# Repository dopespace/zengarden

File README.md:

# zengarden
dope space zen garden is a set of star lanterns that move up and down in the the  Georgia Tech Architecture West building atrium

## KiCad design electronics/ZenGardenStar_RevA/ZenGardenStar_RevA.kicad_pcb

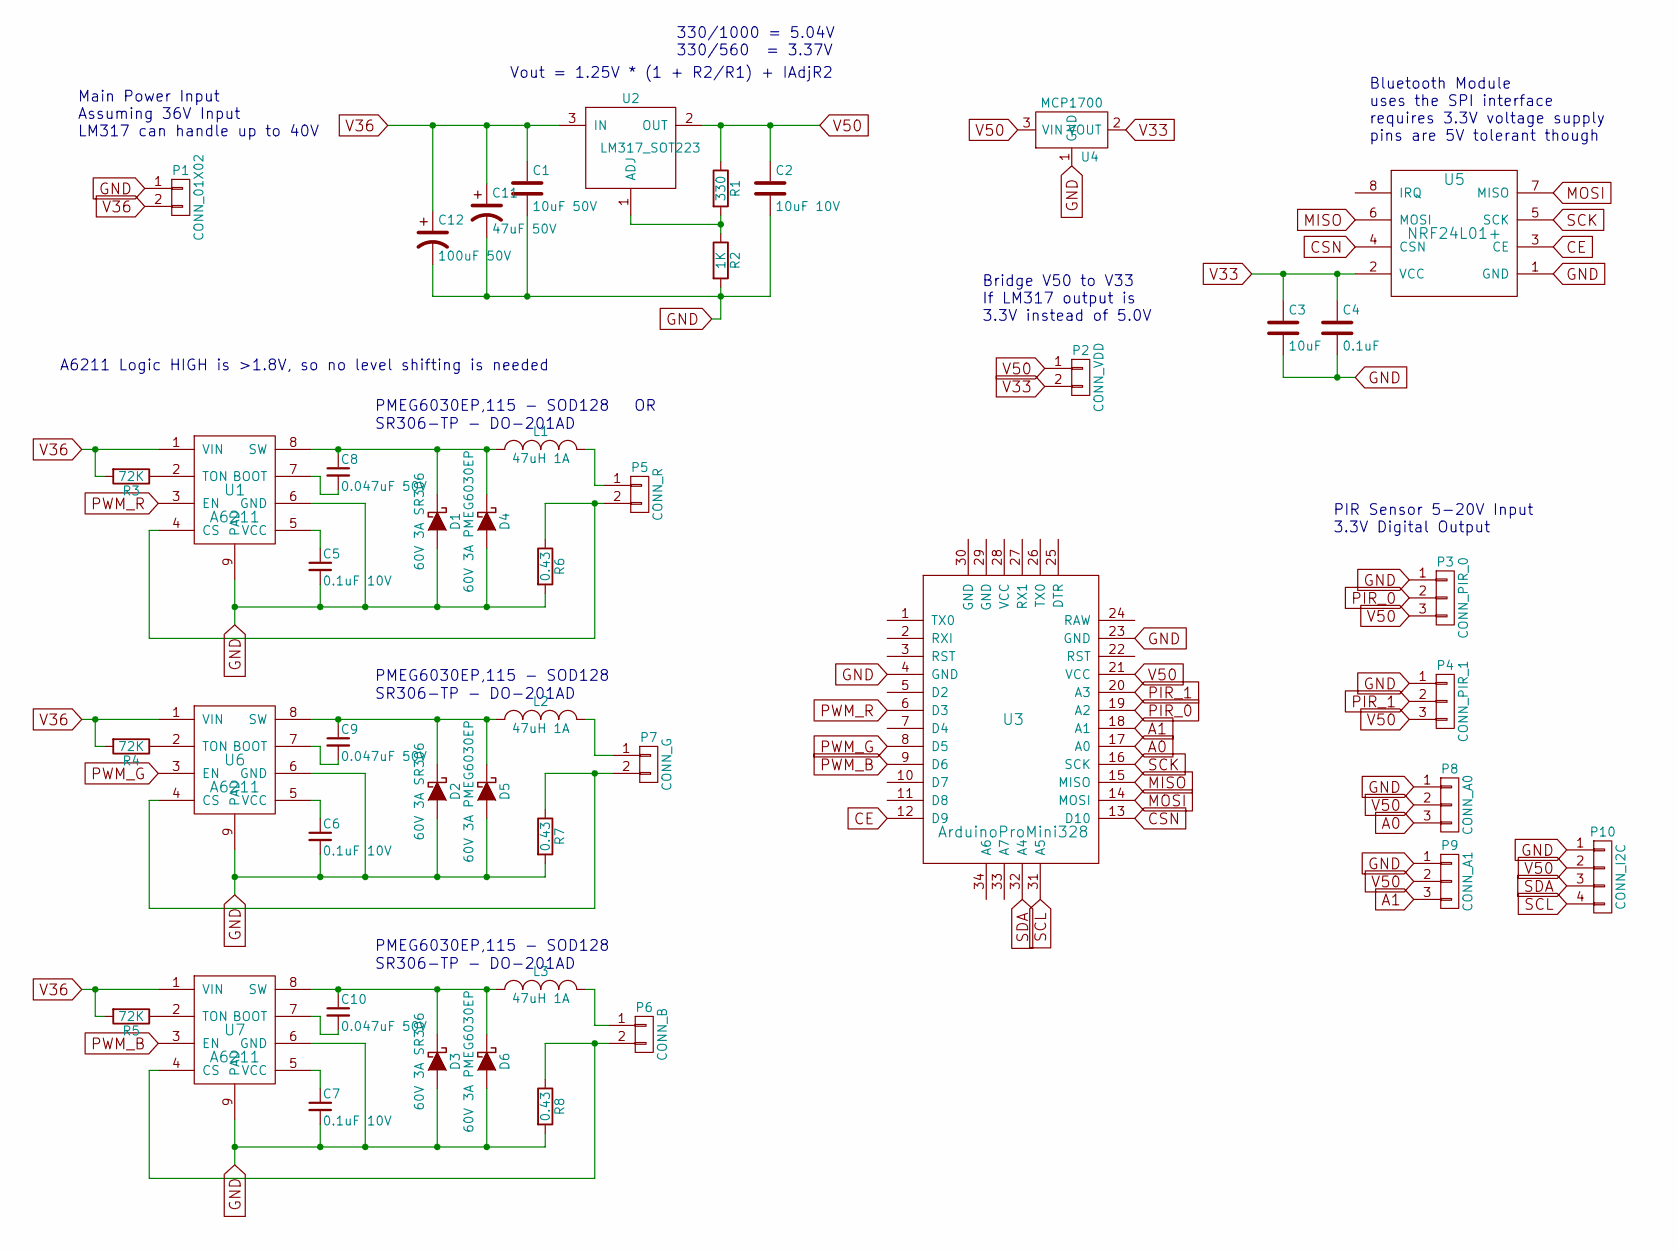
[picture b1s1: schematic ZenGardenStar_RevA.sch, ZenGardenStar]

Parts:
C1: 10uF 50V; C_1206
C2: 10uF 10V; C_1206
C3: 10uF; C_1206
C4: 0.1uF; C_0805
C5, C6, C7: 0.1uF 10V; C_0805
C8, C9, C10: 0.047uF 50V; C_0805
C11: 47uF 50V; C_Radial_D7.5_L11.2_P2.5
C12: 100uF 50V; C_Radial_D8_L13_P3.8
D1, D2, D3: 60V 3A SR306; Diode_DO-201AD_Horizontal_RM15
D4, D5, D6: 60V 3A PMEG6030EP; SOD-123
L1, L2, L3: 47uH 1A; TAIYO_YUDEN_IND_6045
P1: CONN_01X02; AK300-2
P2: CONN_VDD; Pin_Header_Straight_1x02
P3: CONN_PIR_0; Pin_Header_Straight_1x03
P4: CONN_PIR_1; Pin_Header_Straight_1x03
P5: CONN_R; AK300-2
P6: CONN_B; AK300-2
P7: CONN_G; AK300-2
P8: CONN_A0; Pin_Header_Straight_1x03
P9: CONN_A1; Pin_Header_Straight_1x03
P10: CONN_I2C; Pin_Header_Straight_1x04
R1: 330; R_1206
R2: 1K; R_1206
R3, R4, R5: 72K; R_1206
R6, R7, R8: 0.43; R_1206
U1, U6, U7: A6211; SOIC-8-1EP_3.9x4.9mm_Pitch1.27mm
U2: LM317_SOT223; SOT-223
U3: ArduinoProMini328
U4: MCP1700; SOT-23
U5: NRF24L01+

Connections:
A0: P8.3, U3.17 (A0)
A1: P9.3, U3.18 (A1)
CE: U3.12 (D9), U5.3 (CE)
CSN: U3.13 (D10), U5.4 (CSN)
GND: C1.2, C2.2, C3.2, C4.2, C5.2, C6.2, C7.2, C11.2, C12.2, D1.2 (A), D2.2 (A), D3.2 (A), D4.2 (A), D5.2 (A), D6.2 (A), P1.1, P3.1, P4.1, P8.1, P9.1, P10.1, R2.2, R6.2, R7.2, R8.2, U1.6 (GND), U1.9 (PAD), U3.4 (GND), U3.23 (GND), U4.1 (GND), U5.1 (GND), U6.6 (GND), U6.9 (PAD), U7.6 (GND), U7.9 (PAD)
MISO: U3.15 (MISO), U5.6 (MOSI)
MOSI: U3.14 (MOSI), U5.7 (MISO)
unnamed: C5.1, U1.5 (VCC)
unnamed: C6.1, U6.5 (VCC)
unnamed: C7.1, U7.5 (VCC)
unnamed: C8.1, D1.1 (K), D4.1 (K), L1.1, U1.8 (SW)
unnamed: C8.2, U1.7 (BOOT)
unnamed: C9.1, D2.1 (K), D5.1 (K), L2.1, U6.8 (SW)
unnamed: C9.2, U6.7 (BOOT)
unnamed: C10.1, D3.1 (K), D6.1 (K), L3.1, U7.8 (SW)
unnamed: C10.2, U7.7 (BOOT)
unnamed: L1.2, P5.1
unnamed: L2.2, P7.1
unnamed: L3.2, P6.1
unnamed: P5.2, R6.1, U1.4 (CS)
unnamed: P6.2, R8.1, U7.4 (CS)
unnamed: P7.2, R7.1, U6.4 (CS)
unnamed: R1.2, R2.1, U2.1 (ADJ)
unnamed: R3.1, U1.2 (TON)
unnamed: R4.1, U6.2 (TON)
unnamed: R5.1, U7.2 (TON)
PIR_0: P3.2, U3.19 (A2)
PIR_1: P4.2, U3.20 (A3)
PWM_B: U3.9 (D6), U7.3 (EN)
PWM_G: U3.8 (D5), U6.3 (EN)
PWM_R: U1.3 (EN), U3.6 (D3)
SCK: U3.16 (SCK), U5.5 (SCK)
SCL: P10.4, U3.31 (A5)
SDA: P10.3, U3.32 (A4)
V33: C3.1, C4.1, P2.2, U4.2 (VOUT), U5.2 (VCC)
V36: C1.1, C11.1, C12.1, P1.2, R3.2, R4.2, R5.2, U1.1 (VIN), U2.3 (IN), U6.1 (VIN), U7.1 (VIN)
V50: C2.1, P2.1, P3.3, P4.3, P8.2, P9.2, P10.2, R1.1, U2.2 (OUT), U3.21 (VCC), U4.3 (VIN)

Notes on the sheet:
Bluetooth Module uses the SPI interface requires 3.3V voltage supply pins are 5V tolerant though
Vout = 1.25V * (1 + R2/R1) + IAdjR2
330/1000 = 5.04V 330/560 = 3.37V
Bridge V50 to V33 If LM317 output is 3.3V instead of 5.0V
Main Power Input Assuming 36V Input LM317 can handle up to 40V
A6211 Logic HIGH is >1.8V, so no level shifting is needed
PMEG6030EP,115 - SOD128 OR
SR306-TP - DO-201AD
PMEG6030EP,115 - SOD128
PIR Sensor 5-20V Input 3.3V Digital Output

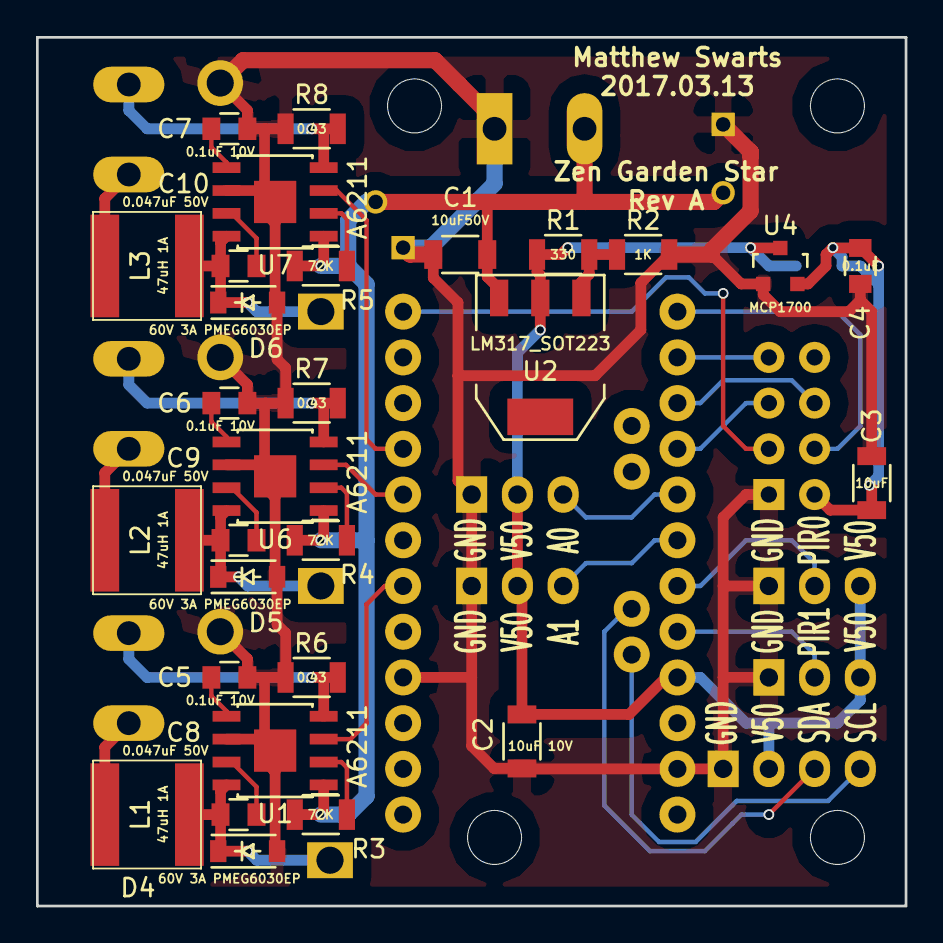
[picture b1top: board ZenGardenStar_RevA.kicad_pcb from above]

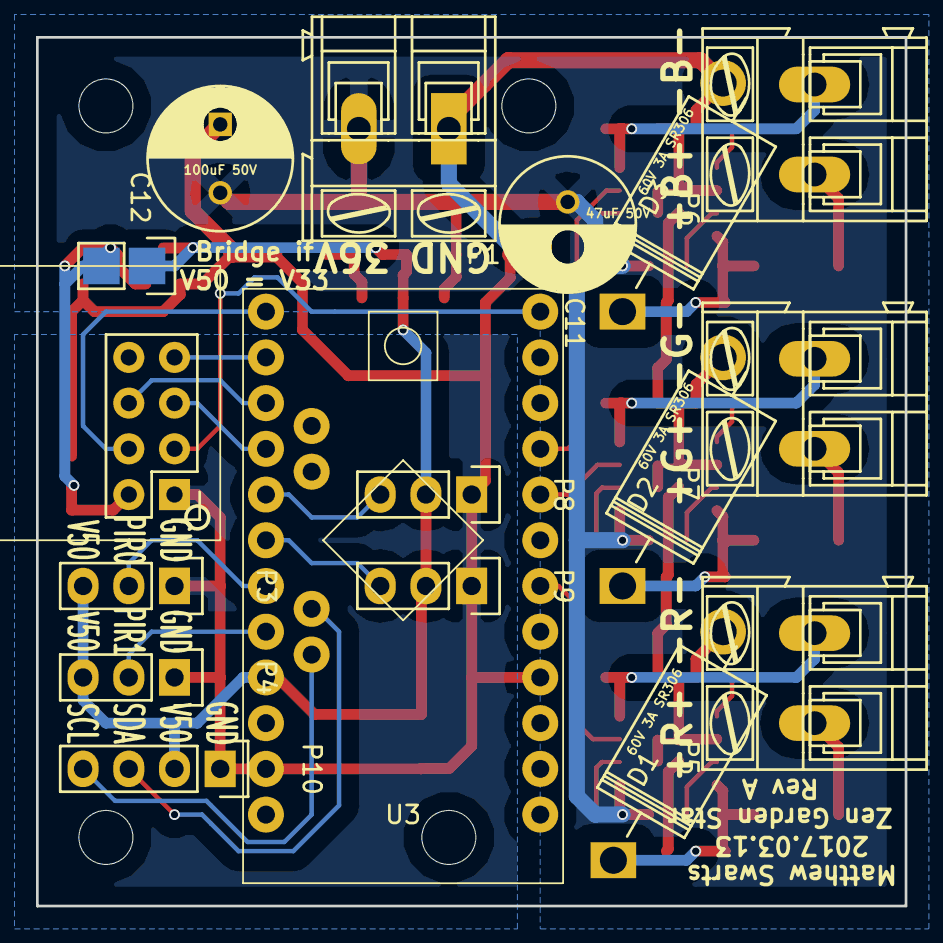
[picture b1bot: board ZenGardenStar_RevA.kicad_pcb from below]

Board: 2 copper layers, 48.3 x 48.3 mm, 46 parts (17 on the bottom side), 37 nets.

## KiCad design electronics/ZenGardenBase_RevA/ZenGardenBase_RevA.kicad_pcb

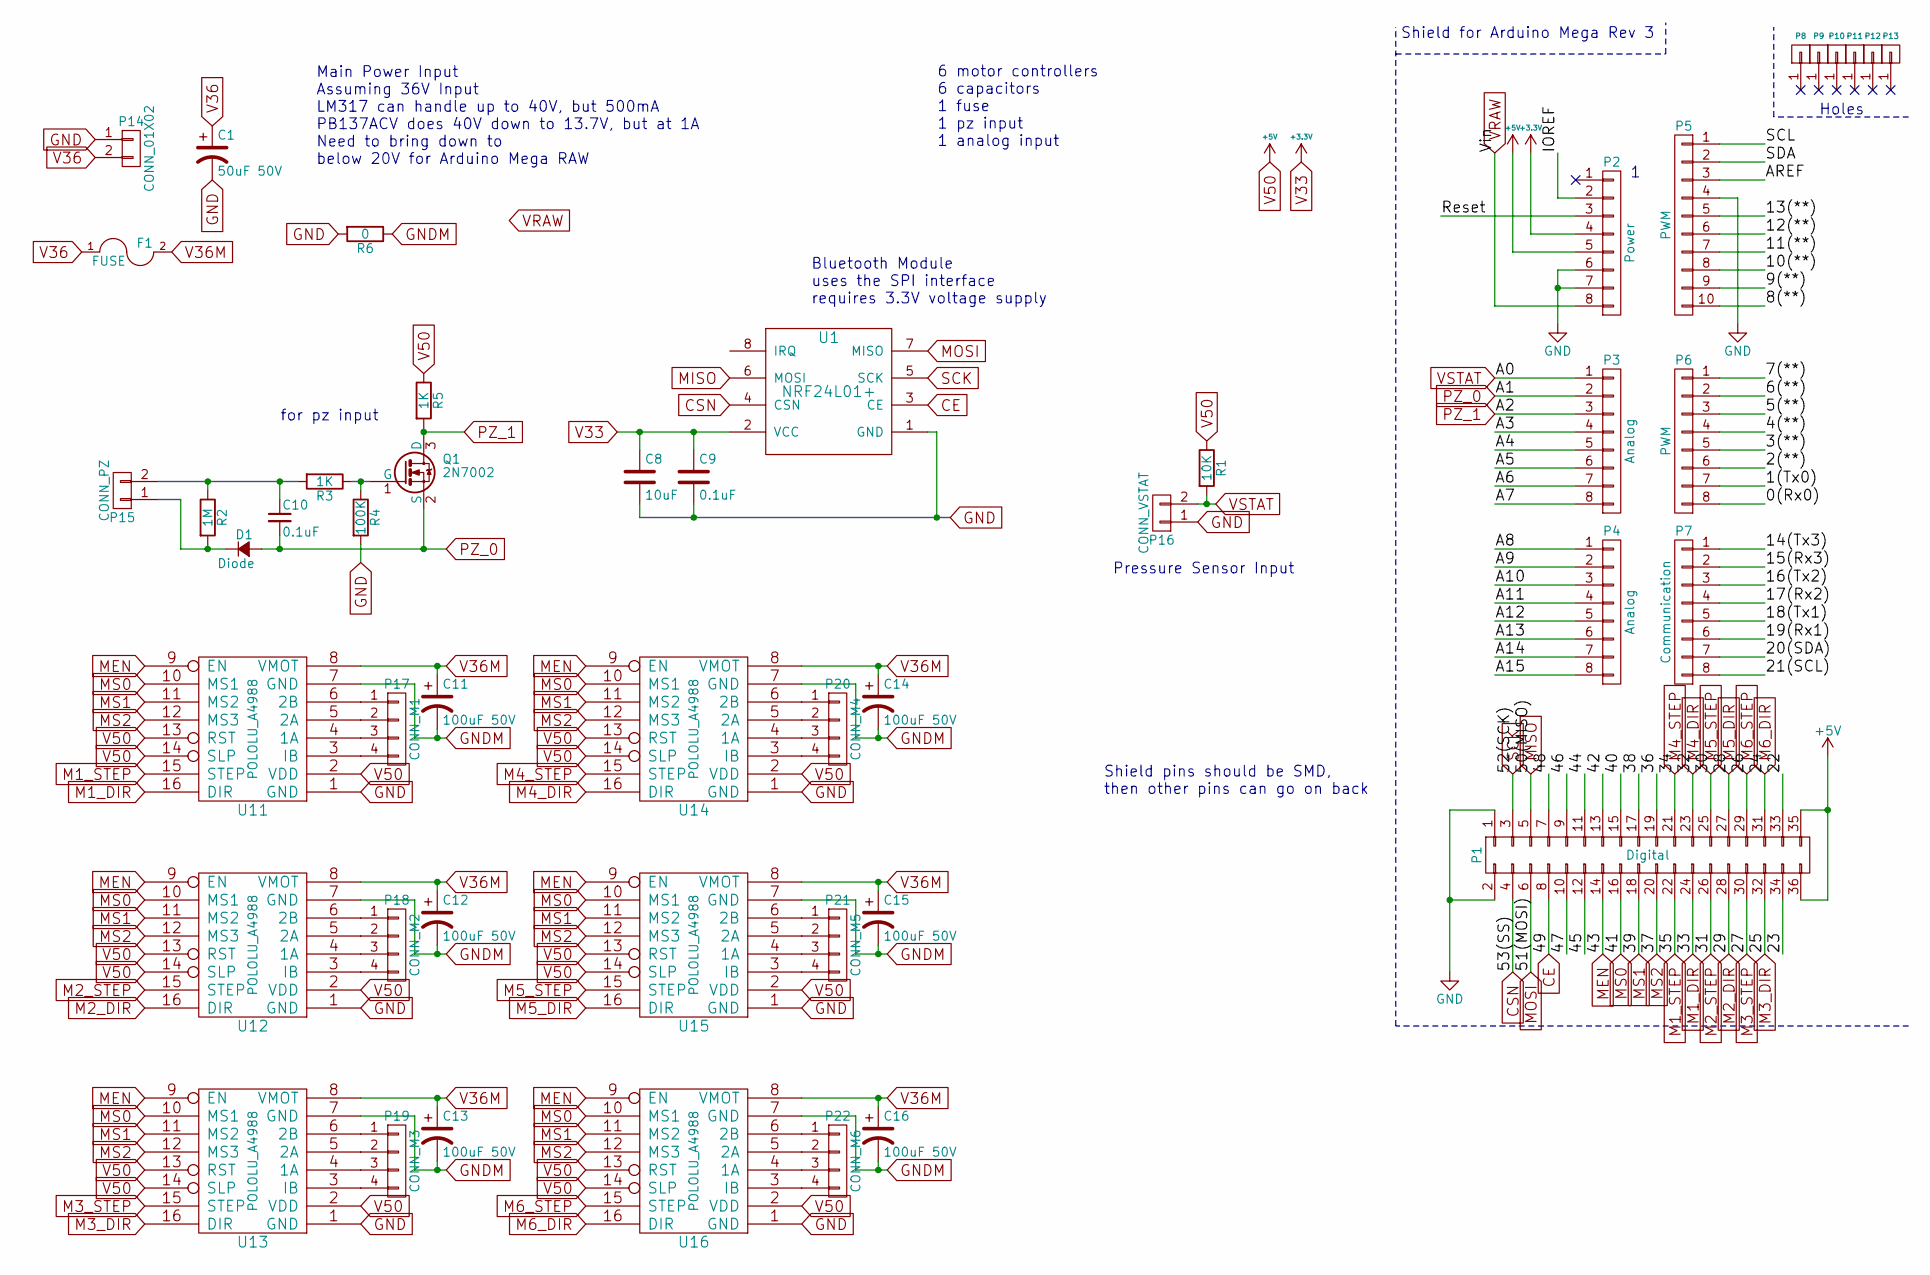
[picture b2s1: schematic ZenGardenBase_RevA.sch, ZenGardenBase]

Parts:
C1: 50uF 50V; C_Radial_D6.3_L11.2_P2.5
C8: 10uF; C_1206
C9, C10: 0.1uF; C_0805
C11, C12, C13, C14, C15, C16: 100uF 50V; C_Radial_D8_L13_P3.8
D1: Diode; SOD-123
F1: FUSE; Fuse_TE5_Littlefuse-395Series
P1: Digital; Socket_Strip_Arduino_2x18
P2: Power; Socket_Strip_Arduino_1x08
P3, P4: Analog; Socket_Strip_Arduino_1x08
P5: PWM; Socket_Strip_Arduino_1x10
P6: PWM; Socket_Strip_Arduino_1x08
P7: Communication; Socket_Strip_Arduino_1x08
P8, P9, P10, P11, P12, P13: CONN_01X01; Arduino_1pin
P14: CONN_01X02; AK300-2
P15: CONN_PZ; Pin_Header_Straight_1x02
P16: CONN_VSTAT; Pin_Header_Straight_1x02
P17: CONN_M1; AK300-4
P18: CONN_M2; AK300-4
P19: CONN_M3; AK300-4
P20: CONN_M4; AK300-4
P21: CONN_M5; AK300-4
P22: CONN_M6; AK300-4
Q1: 2N7002; SOT-23
R1: 10K; R_1206
R2: 1M; R_1206
R3, R5: 1K; R_1206
R4: 100K; R_1206
R6: 0; R_1206
U1: NRF24L01+
U11, U12, U13, U14, U15, U16: POLOLU_A4988; SWDIP8_.6W

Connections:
/0(Rx0): P6.8
/1(Tx0): P6.7
/2(**): P6.6
/3(**): P6.5
/4(**): P6.4
/5(**): P6.3
/6(**): P6.2
/7(**): P6.1
/8(**): P5.10
/9(**): P5.9
/10(**): P5.8
/11(**): P5.7
/12(**): P5.6
/13(**): P5.5
/14(Tx3): P7.1
/15(Rx3): P7.2
/16(Tx2): P7.3
/17(Rx2): P7.4
/18(Tx1): P7.5
/19(Rx1): P7.6
/20(SDA): P7.7
/21(SCL): P7.8
/22: P1.33
/23: P1.34
/36: P1.19
/38: P1.17
/40: P1.15
/42: P1.13
/44: P1.11
/45: P1.12
/46: P1.9
/47: P1.10
/48: P1.7
/A3: P3.4
/A4: P3.5
/A5: P3.6
/A6: P3.7
/A7: P3.8
/A8: P4.1
/A9: P4.2
/A10: P4.3
/A11: P4.4
/A12: P4.5
/A13: P4.6
/A14: P4.7
/A15: P4.8
/AREF: P5.3
/IOREF: P2.2
/Reset: P2.3
/SCL: P5.1
/SDA: P5.2
CE: P1.8, U1.3 (CE)
CSN: P1.4, U1.4 (CSN)
GND: C1.2, C8.2, C9.2, P1.1, P1.2, P2.6, P2.7, P5.4, P14.1, P16.1, R4.2, R6.2, U1.1 (GND), U11.1 (GND), U12.1 (GND), U13.1 (GND), U14.1 (GND), U15.1 (GND), U16.1 (GND)
GNDM: C11.2, C12.2, C13.2, C14.2, C15.2, C16.2, R6.1, U11.7 (GND), U12.7 (GND), U13.7 (GND), U14.7 (GND), U15.7 (GND), U16.7 (GND)
M1_DIR: P1.24, U11.16 (DIR)
M1_STEP: P1.22, U11.15 (STEP)
M2_DIR: P1.28, U12.16 (DIR)
M2_STEP: P1.26, U12.15 (STEP)
M3_DIR: P1.32, U13.16 (DIR)
M3_STEP: P1.30, U13.15 (STEP)
M4_DIR: P1.23, U14.16 (DIR)
M4_STEP: P1.21, U14.15 (STEP)
M5_DIR: P1.27, U15.16 (DIR)
M5_STEP: P1.25, U15.15 (STEP)
M6_DIR: P1.31, U16.16 (DIR)
M6_STEP: P1.29, U16.15 (STEP)
MEN: P1.14, U11.9 (EN), U12.9 (EN), U13.9 (EN), U14.9 (EN), U15.9 (EN), U16.9 (EN)
MISO: P1.5, U1.6 (MOSI)
MOSI: P1.6, U1.7 (MISO)
MS0: P1.16, U11.10 (MS1), U12.10 (MS1), U13.10 (MS1), U14.10 (MS1), U15.10 (MS1), U16.10 (MS1)
MS1: P1.18, U11.11 (MS2), U12.11 (MS2), U13.11 (MS2), U14.11 (MS2), U15.11 (MS2), U16.11 (MS2)
MS2: P1.20, U11.12 (MS3), U12.12 (MS3), U13.12 (MS3), U14.12 (MS3), U15.12 (MS3), U16.12 (MS3)
unnamed: C10.1, P15.2, R2.1, R3.2
unnamed: D1.1 (K), P15.1, R2.2
unnamed: P17.1, U11.6 (2B)
unnamed: P17.2, U11.5 (2A)
unnamed: P17.3, U11.4 (1A)
unnamed: P17.4, U11.3 (IB)
unnamed: P18.1, U12.6 (2B)
unnamed: P18.2, U12.5 (2A)
unnamed: P18.3, U12.4 (1A)
unnamed: P18.4, U12.3 (IB)
unnamed: P19.1, U13.6 (2B)
unnamed: P19.2, U13.5 (2A)
unnamed: P19.3, U13.4 (1A)
unnamed: P19.4, U13.3 (IB)
unnamed: P20.1, U14.6 (2B)
unnamed: P20.2, U14.5 (2A)
unnamed: P20.3, U14.4 (1A)
unnamed: P20.4, U14.3 (IB)
unnamed: P21.1, U15.6 (2B)
unnamed: P21.2, U15.5 (2A)
unnamed: P21.3, U15.4 (1A)
unnamed: P21.4, U15.3 (IB)
unnamed: P22.1, U16.6 (2B)
unnamed: P22.2, U16.5 (2A)
unnamed: P22.3, U16.4 (1A)
unnamed: P22.4, U16.3 (IB)
unnamed: Q1.1 (G), R3.1, R4.1
PZ_0: C10.2, D1.2 (A), P3.2, Q1.2 (S)
PZ_1: P3.3, Q1.3 (D), R5.2
SCK: P1.3, U1.5 (SCK)
V33: C8.1, C9.1, P2.4, U1.2 (VCC)
V36: C1.1, F1.1, P14.2
V36M: C11.1, C12.1, C13.1, C14.1, C15.1, C16.1, F1.2, U11.8 (VMOT), U12.8 (VMOT), U13.8 (VMOT), U14.8 (VMOT), U15.8 (VMOT), U16.8 (VMOT)
V50: P1.35, P1.36, P2.5, R1.1, R5.1, U11.2 (VDD), U11.13 (RST), U11.14 (SLP), U12.2 (VDD), U12.13 (RST), U12.14 (SLP), U13.2 (VDD), U13.13 (RST), U13.14 (SLP), U14.2 (VDD), U14.13 (RST), U14.14 (SLP), U15.2 (VDD), U15.13 (RST), U15.14 (SLP), U16.2 (VDD), U16.13 (RST), U16.14 (SLP)
VRAW: P2.8
VSTAT: P3.1, P16.2, R1.2

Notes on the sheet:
Shield for Arduino Mega Rev 3
Holes
6 motor controllers 6 capacitors 1 fuse 1 pz input 1 analog input
Main Power Input Assuming 36V Input LM317 can handle up to 40V, but 500mA PB137ACV does 40V down to 13.7V, but at 1A Need to bring down to below 20V for Arduino Mega RAW
for pz input
Shield pins should be SMD, then other pins can go on back
Bluetooth Module uses the SPI interface requires 3.3V voltage supply
Pressure Sensor Input

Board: 2 copper layers, 48 parts (0 on the bottom side), 57 nets, no tracks yet.

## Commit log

2017-03-07 added first draft of star board
2017-03-09 updated schematic for star
2017-03-09 updated star layout and schematic and render, at 80-90% done
2017-03-09 added start of the base mega shield
2017-03-10 updated base schematic and layout to show that it will be easier to do on a breadboard
2017-03-11 some updates to the star schematics and layout; schematic pretty much final
2017-03-13 near final pcb layout
2017-03-13 final pcb layout ready, gerbers created, order prepared
2017-03-13 added renders of the star pcb
2017-04-04 added first version of star firmware for color test
2017-04-22 Added code for arduino Mega 2560
